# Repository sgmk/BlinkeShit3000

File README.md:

### BlinkeShit 3000

# New BlinkeShit for Bitwäscherei

An adapted and simplified version of the circuit of the 8Bit Mixtape / Gär-Lämpli to make a little BlinkeShit sign for our new hackerspace collective.

https://github.com/8BitMixtape/8Bit-Mixtape-NEO

You can design your custom front plate and etch it on PCB or use any other material, paper etc as diffusor.

Upload different BlinkeCode using the Audio Bootloader from arduino IDE:
https://github.com/ChrisMicro/TinyAudioBoot
Best to directly install the full hardware library of the 8bitMixtape to your Arduino IDE, add this to your additional hardware manager: http://8bitmixtape.github.io/package_8bitmixtape_index.json

There are more pins available for adding sensors, pots, buttons etc.

## PCB baseplate

# SGMK X-mas Party "Make DOCK18 Bright Again"
###### Shenzhen is soooo last millenium

(taken from Oli W. website: http://oliverwalkhoff.com/led-chase-light)

# 2019 Entries for BlinkeShit 3000

## International Jury for SGMK BlinkeShit

* David Chen (Taiwan) - openlab Taipei, co-developer of the Taiwanduino
* Scott Beibin (USA) - ...
* Miranda Moss (S.Africa / Sweden) - tries-not-to-be-an-artist, makes solar-powered blinking ginger-roots
* Daniel Eugene Lacey-McDermott (Norway) - Captain Credible
* Yair Reshef (Israel) - Idiot (representing Denisa Kera (global) - PCB connaisseuse and philosopher)
* absent: Budi Prakosa (Indonesia) - Manticore / BadGeek, developer of svg2shenzhen (and much more)

Live Video stream: https://meet.jit.si/BlinkeShit3000-international-jury

## Almost complete selection of entries

Author: anonymous

Author: Salome K. in the name of raumschiff

Author: Felix Bänteli and Sunrise not really sponsored 

Author: Markus S.

(Free Energy with Mario Purkathofer)

Author: Unknown

Author: Christoph K.

Author: Neighbour (Name unknown)

Author: Gaudi. We are still considering to ban Urs Gaudenz from this competition!

Author: Marc D. aka dusjagr

Author: Gaudi present for Veli

Author: Oliver Jäggi soon to become "a legend"

Author: Tillo

Author: Katrin

# Available components in MechArtLab

## "Official" SGMK BlinkeShit footprint library for KiCAD

See folder... still in progress

## Blinke LEDs RGB

## Blinke Flash LEDs various colours

## NOT-Blinking classic top-LEDs 3528

(for our more-epileptic friends)

## Blinke Pots

Datashit: https://github.com/sgmk/BlinkeShit3000/raw/master/orders%20vom%20ali/RV09BF.pdf

# Classic Examples by the Pioneers of BlinkeShit
## by GaudiLabs

https://github.com/GaudiLabs/BitBadge

## by Gandalf
coming soon...

## by Oli W. "The Legend"
This is one of the first electronic circuits he built, dated October 1982.

(LED chase light, 1982, taken from his website: http://oliverwalkhoff.com/led-chase-light)

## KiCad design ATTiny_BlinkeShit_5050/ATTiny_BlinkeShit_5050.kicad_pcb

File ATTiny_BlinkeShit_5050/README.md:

# AI-tiny BlinkeShit 3000

Nice little 4x5 pixel display with ATTINY85, Audio bootloader, and (new) 5050 WS2812b RGB LEDs.

## SMD Reflow Workshop

This workshop is primarily to introduce beginners into a very DIY style of reflow soldering using a small number of parts, self-etched PCBs, self-made stencils and simple heaters for reflowing.

## AI slop on 20 pixels

more about this soon!

Visuals can be uploaded from this site: https://dusjagr.github.io/AudioBoot-pio-test/wav/index.html

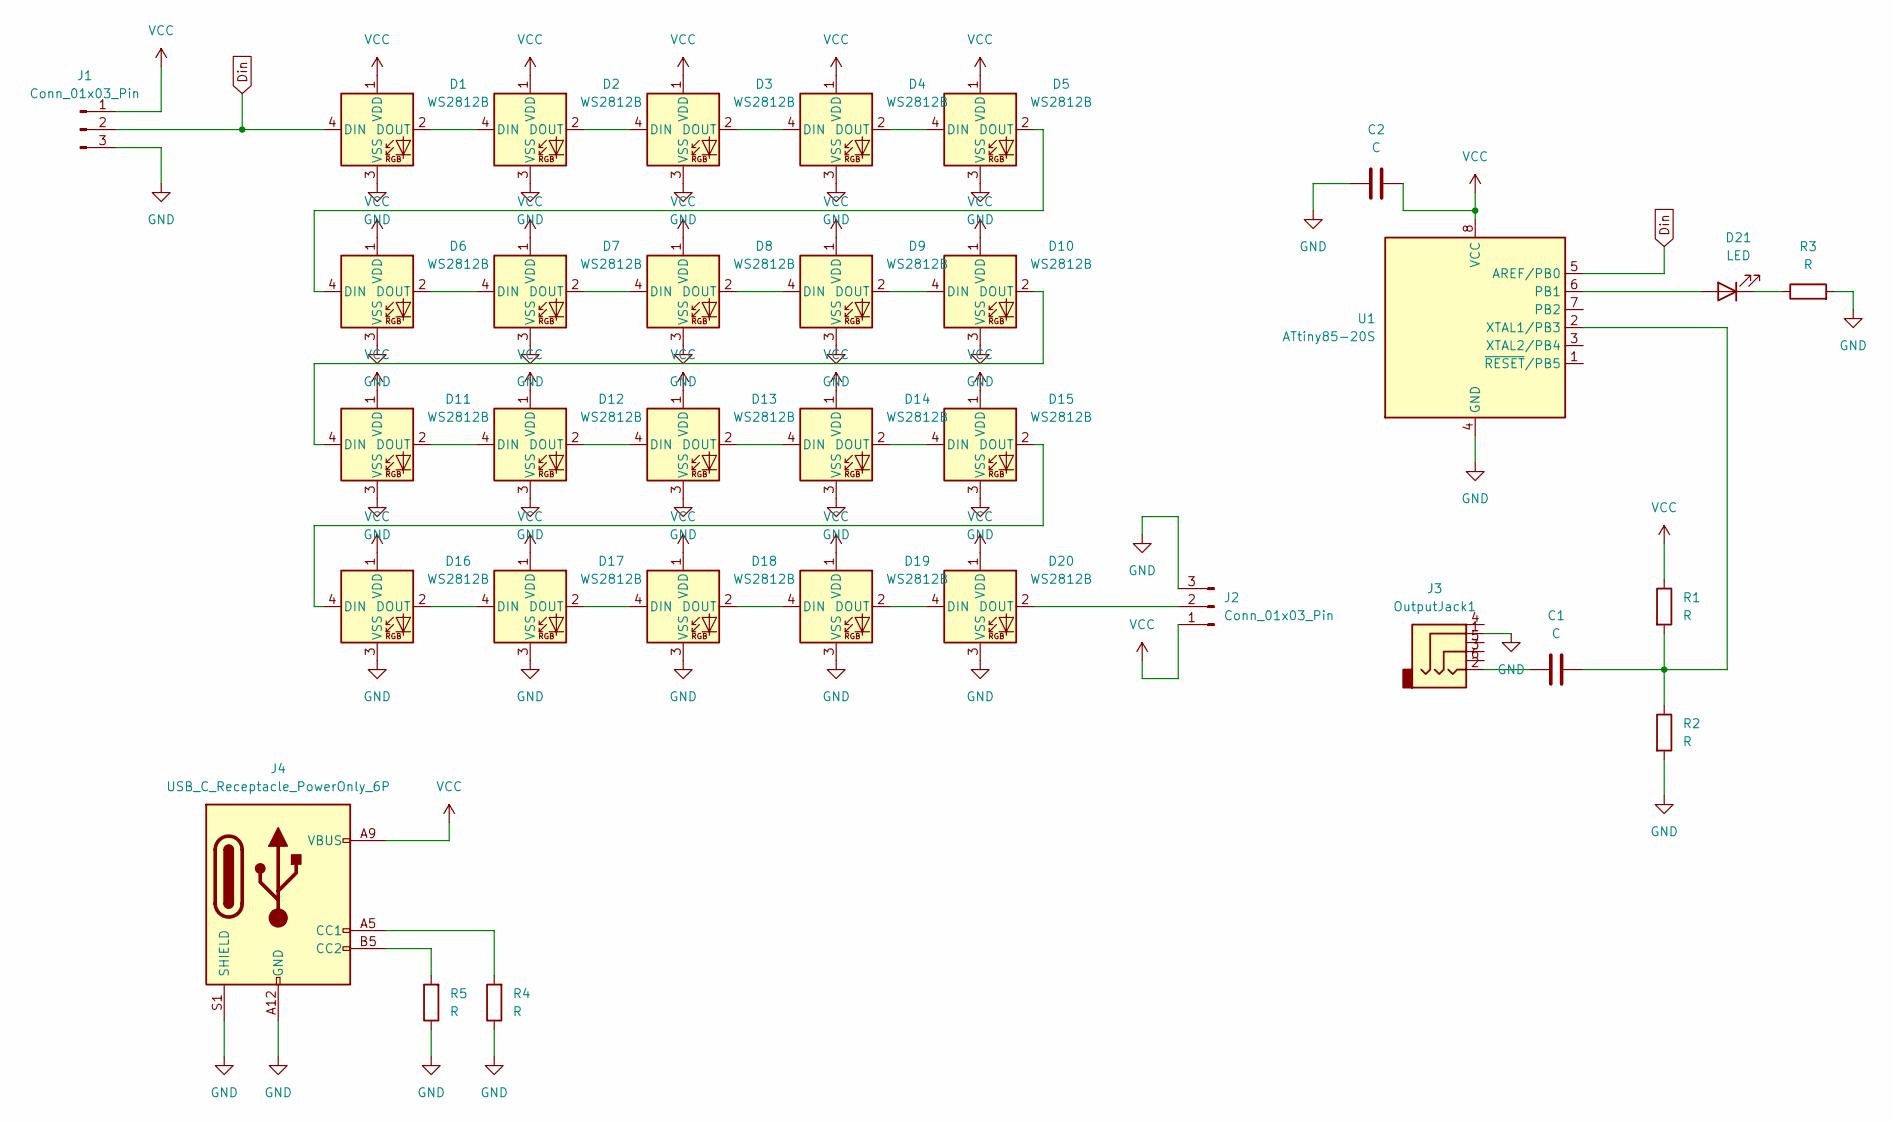
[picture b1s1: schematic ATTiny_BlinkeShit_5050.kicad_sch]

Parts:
C1, C2: C; C_1210_noGND
D1, D2, D3, D4, D5, D6, D7, D8, D9, D10, D11, D12, D13, D14, D15, D16, D17, D18, D19, D20: WS2812B; Mixtape_NEO_WS2812B_3d
D21: LED; LED_PLCC_2835_Handsoldering
J1, J2: Conn_01x03_Pin; PinSocket_1x03_P2.54mm_Vertical
J3: OutputJack1; 3.5mm_jack_SMT_dusjagrNew
J4: USB_C_Receptacle_PowerOnly_6P; USB_C_Receptacle_GCT_USB4135-GF-A_6P_TopMnt_Horizontal
R1, R2: R; R_1206_noGND
R3, R4, R5: R; R_1206_noGND_noSilk
U1: ATtiny85-20S; SOIC-8W_5.3x5.3mm_P1.27mm

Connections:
Din: D1.4 (DIN), J1.2, U1.5 (AREF/PB0)
GND: C2.1, D1.3 (VSS), D2.3 (VSS), D3.3 (VSS), D4.3 (VSS), D5.3 (VSS), D6.3 (VSS), D7.3 (VSS), D8.3 (VSS), D9.3 (VSS), D10.3 (VSS), D11.3 (VSS), D12.3 (VSS), D13.3 (VSS), D14.3 (VSS), D15.3 (VSS), D16.3 (VSS), D17.3 (VSS), D18.3 (VSS), D19.3 (VSS), D20.3 (VSS), J1.3, J2.3, J3.1, J4.A12 (GND), J4.B12 (GND), J4.S1 (SHIELD), R2.2, R3.2, R4.1, R5.1, U1.4 (GND)
unnamed: C1.1, J3.2
unnamed: D1.2 (DOUT), D2.4 (DIN)
unnamed: D2.2 (DOUT), D3.4 (DIN)
unnamed: D3.2 (DOUT), D4.4 (DIN)
unnamed: D4.2 (DOUT), D5.4 (DIN)
unnamed: D5.2 (DOUT), D6.4 (DIN)
unnamed: D6.2 (DOUT), D7.4 (DIN)
unnamed: D7.2 (DOUT), D8.4 (DIN)
unnamed: D8.2 (DOUT), D9.4 (DIN)
unnamed: D9.2 (DOUT), D10.4 (DIN)
unnamed: D10.2 (DOUT), D11.4 (DIN)
unnamed: D11.2 (DOUT), D12.4 (DIN)
unnamed: D12.2 (DOUT), D13.4 (DIN)
unnamed: D13.2 (DOUT), D14.4 (DIN)
unnamed: D14.2 (DOUT), D15.4 (DIN)
unnamed: D15.2 (DOUT), D16.4 (DIN)
unnamed: D16.2 (DOUT), D17.4 (DIN)
unnamed: D17.2 (DOUT), D18.4 (DIN)
unnamed: D18.2 (DOUT), D19.4 (DIN)
unnamed: D19.2 (DOUT), D20.4 (DIN)
unnamed: D20.2 (DOUT), J2.2
unnamed: D21.2 (A), U1.6 (PB1)
unnamed: D21.1 (K), R3.1
unnamed: J4.A5 (CC1), R4.2
unnamed: J4.B5 (CC2), R5.2
unnamed: C1.2, R1.2, R2.1, U1.2 (XTAL1/PB3)
VCC: C2.2, D1.1 (VDD), D2.1 (VDD), D3.1 (VDD), D4.1 (VDD), D5.1 (VDD), D6.1 (VDD), D7.1 (VDD), D8.1 (VDD), D9.1 (VDD), D10.1 (VDD), D11.1 (VDD), D12.1 (VDD), D13.1 (VDD), D14.1 (VDD), D15.1 (VDD), D16.1 (VDD), D17.1 (VDD), D18.1 (VDD), D19.1 (VDD), D20.1 (VDD), J1.1, J2.1, J4.A9 (VBUS), J4.B9 (VBUS), R1.1, U1.8 (VCC)

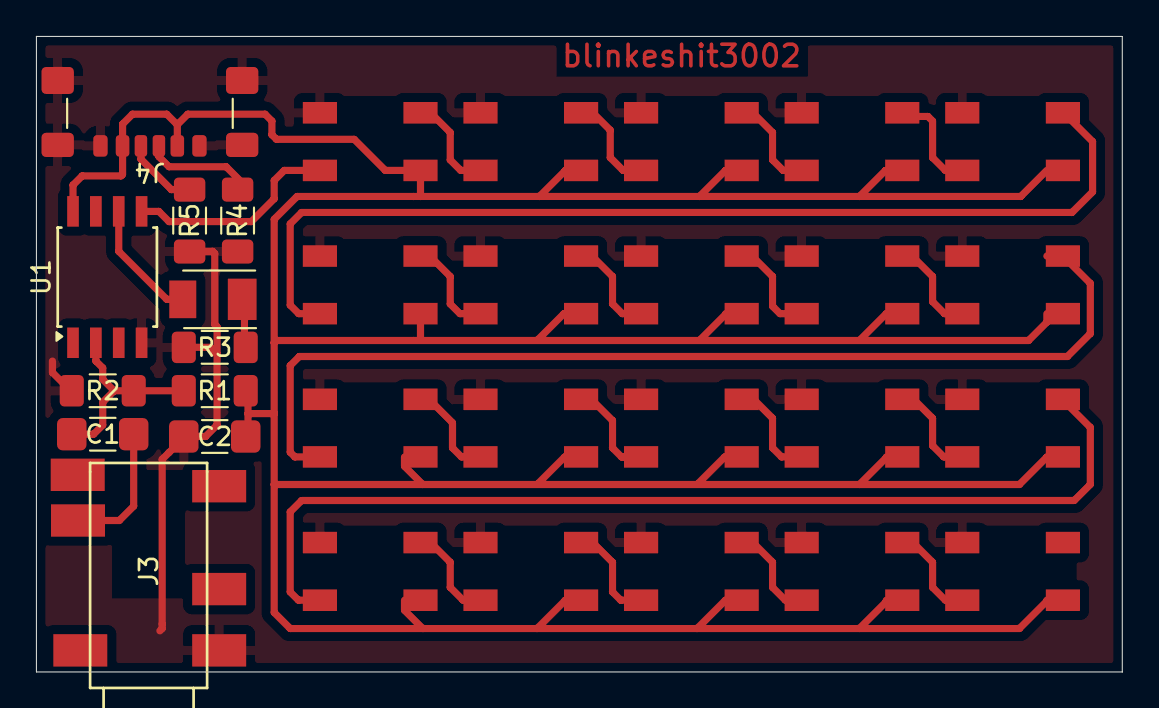
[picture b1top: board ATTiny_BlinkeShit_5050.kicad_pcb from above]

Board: 2 copper layers, 60.3 x 35.3 mm, 31 parts (0 on the bottom side), 28 nets.

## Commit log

2019-11-21 adding screenshots
2019-11-22 added some photos
2019-11-22 editing readme
2019-11-26 adding Kicad files
2019-12-14 2019 Entries
2019-12-14 2019 Entries[A
2020-01-20 maybe new bitbadge
2020-03-04 adding LUMA-box
2020-03-09 new parametric design
2020-06-15 adding the Bitw Blinkeshit
2020-06-15 photos Bitw Blinkeshit
2020-06-15 updating readme
2026-01-02 added new blinkeshit
2026-01-02 updating all
2026-01-05 modified openscad to customize thickness of cover
2026-01-05 added readme for 5050 blinkeshit
2026-01-05 small edits on openscad file
